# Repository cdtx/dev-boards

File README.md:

Some simple home made PCBs

- [ESP-01 prototyping board](./esp01-1/README.md)

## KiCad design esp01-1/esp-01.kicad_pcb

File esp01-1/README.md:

ESP-01 prototyping board
========================

This board allows to discuss an ESP-01 and program it from a USB connected PC.
So it basically embeds a voltage regulator, and a USB/Serial transceiver.
Push buttons allows to switch to bootloader mode.

ESP-01 is the cheapest ESP8266 based iot component, less than 5$
It's only a wifi modem that's driven by [AT commands](https://room-15.github.io/blog/2015/03/26/esp8266-at-command-reference/#AT), no GPIO, no available peripherals.

Typical case is to connect it with an arduino or equivalent discussing AT commands over tx/rx pins.
Flashing a new firmware can be done over tx/rx as well, after a special boot procedure.

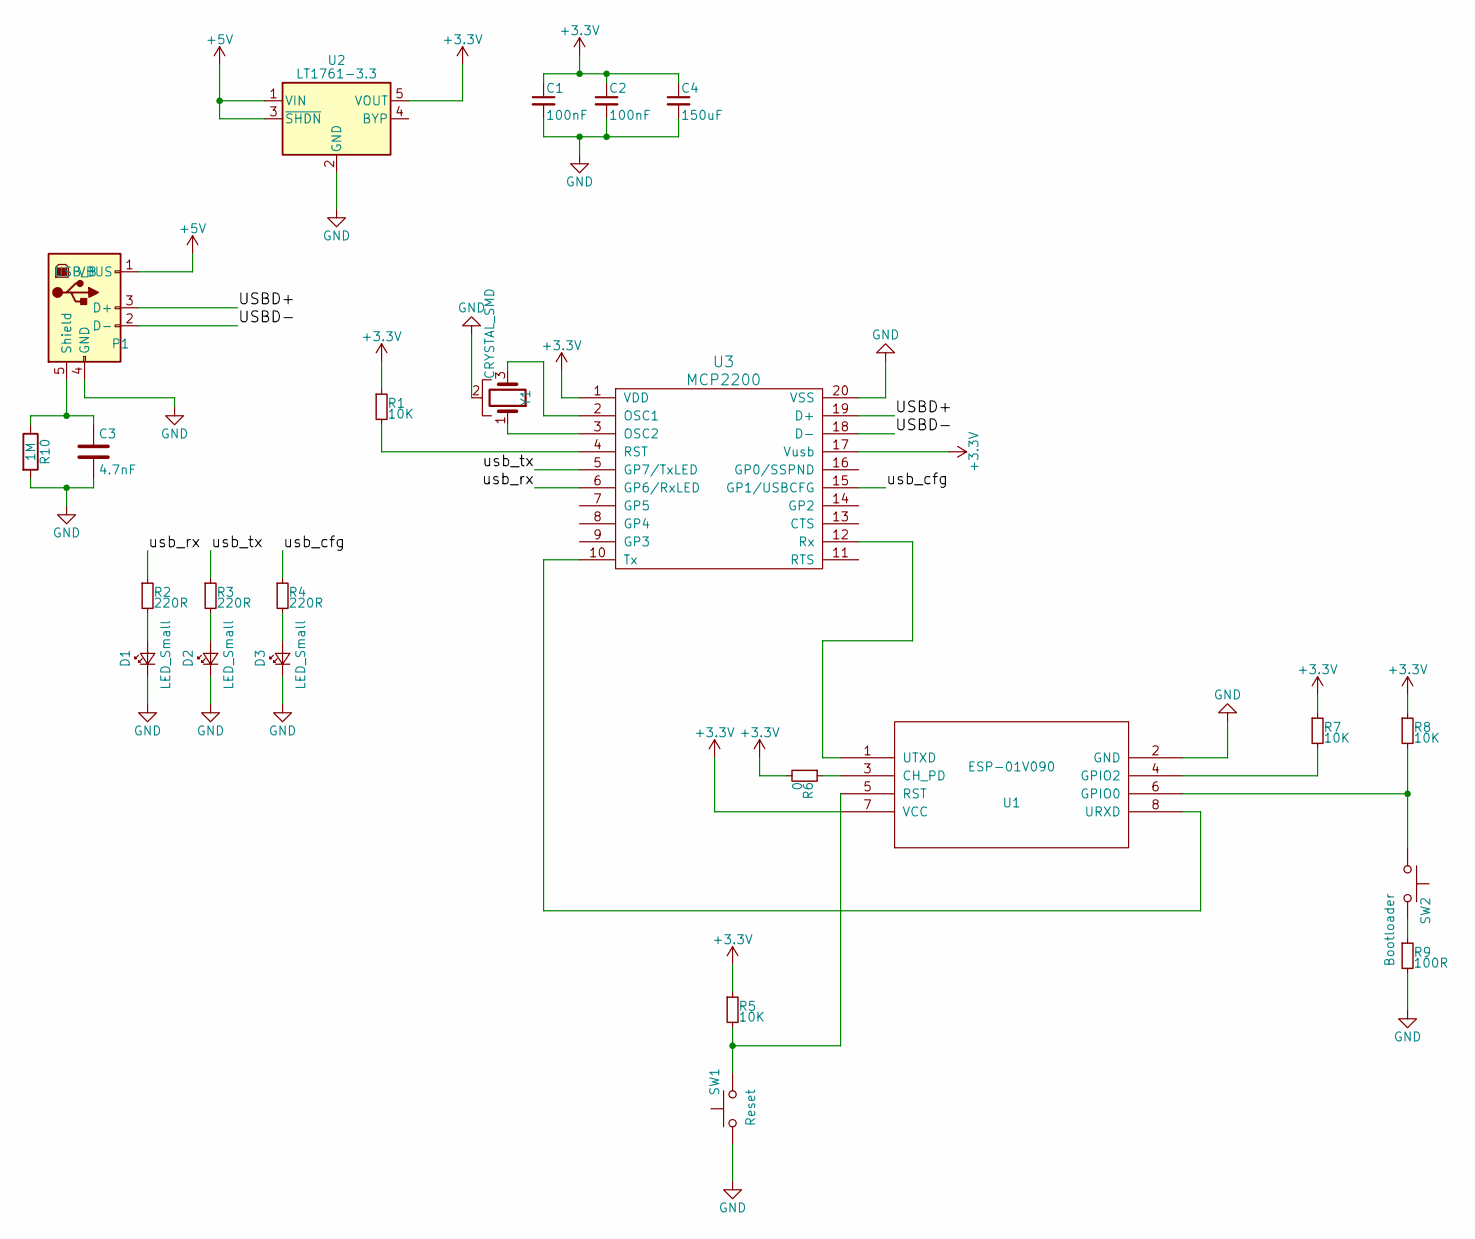
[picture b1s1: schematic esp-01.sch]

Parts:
C1, C2: 100nF; C_0805
C3: 4.7nF; C_Disc_D6_P5
C4: 150uF; C_1210_HandSoldering
D1, D2, D3: LED_Small; LED_1206
P1: USB_B
R1, R7, R8: 10K; Resistor_Horizontal_RM10mm
R2, R3, R4: 220R; Resistor_Horizontal_RM10mm
R5: 10K; R_0603
R6: 0; R_0603
R9: 100R; R_0603
R10: 1M; Resistor_Horizontal_RM10mm
SW1: Reset; SW_PUSH_SMALL
SW2: Bootloader; SW_PUSH_SMALL
U1: ESP-01V090; ESP-01
U2: LT1761-3.3; SOT-23-5
U3: MCP2200; SOIC-20W_7.5x12.8mm_Pitch1.27mm
Y1: CRYSTAL_SMD; Resonator_3.2x1.3mm

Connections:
+3V3: C1.1, C2.1, C4.1, R1.1, R5.1, R6.2, R7.1, R8.1, U1.7 (VCC), U2.5 (VOUT), U3.1 (VDD), U3.17 (Vusb)
+5V: P1.1 (VBUS), U2.1 (VIN), U2.3 (~SHDN)
/USBD+: P1.3 (D+), U3.19 (D+)
/USBD-: P1.2 (D-), U3.18 (D-)
/usb_cfg: R4.1, U3.15 (GP1/USBCFG)
/usb_rx: R2.1, U3.6 (GP6/RxLED)
/usb_tx: R3.1, U3.5 (GP7/TxLED)
GND: C1.2, C2.2, C3.2, C4.2, D1.1 (K), D2.1 (K), D3.1 (K), P1.4 (GND), R9.2, R10.2, SW1.1, U1.2 (GND), U2.2 (GND), U3.20 (VSS), Y1.2
unnamed: C3.1, P1.5 (Shield), R10.1
unnamed: D1.2 (A), R2.2
unnamed: D2.2 (A), R3.2
unnamed: D3.2 (A), R4.2
unnamed: R1.2, U3.4 (RST)
unnamed: R5.2, SW1.2, U1.5 (RST)
unnamed: R6.1, U1.3 (CH_PD)
unnamed: R7.2, U1.4 (GPIO2)
unnamed: R8.2, SW2.1, U1.6 (GPIO0)
unnamed: R9.1, SW2.2
unnamed: U1.1 (UTXD), U3.12 (Rx)
unnamed: U1.8 (URXD), U3.10 (Tx)
unnamed: U3.2 (OSC1), Y1.3
unnamed: U3.3 (OSC2), Y1.1

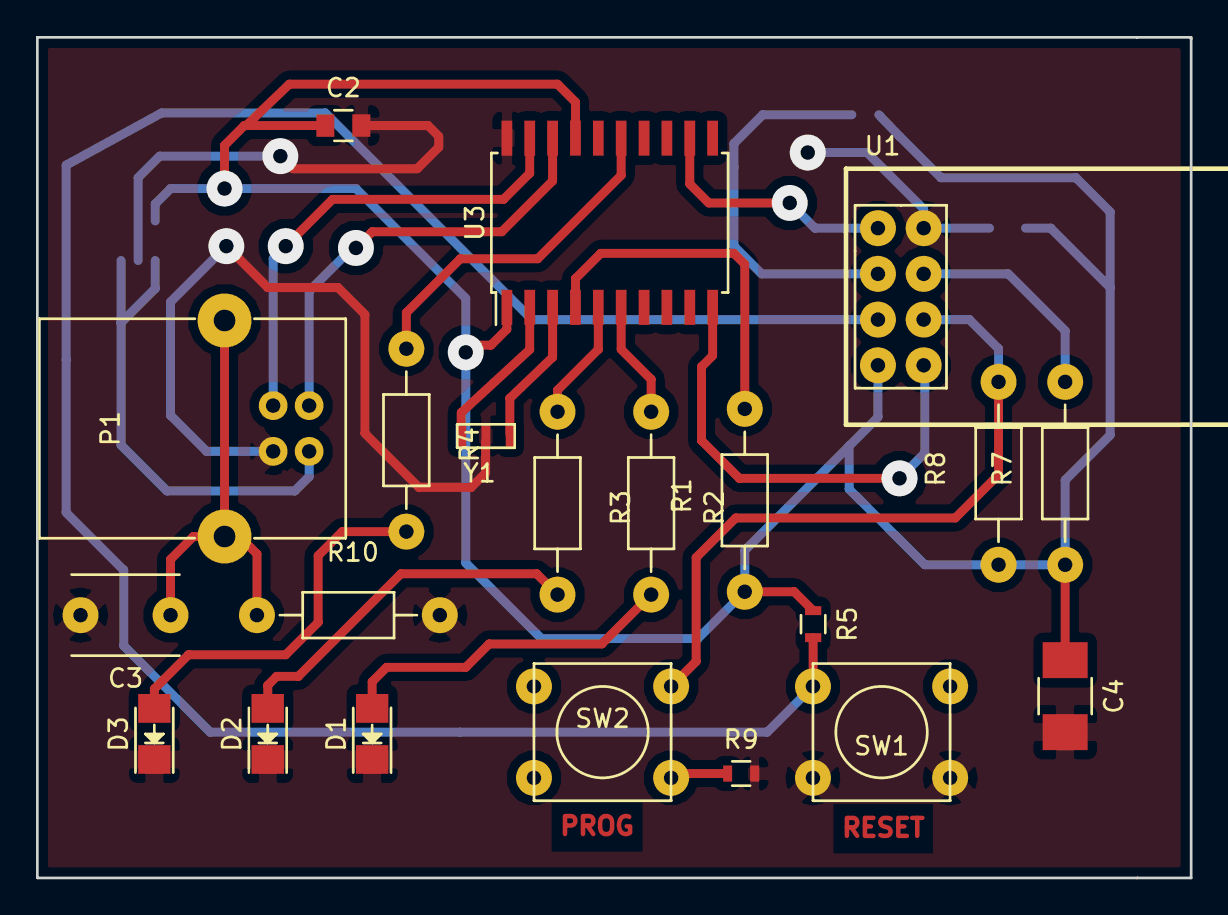
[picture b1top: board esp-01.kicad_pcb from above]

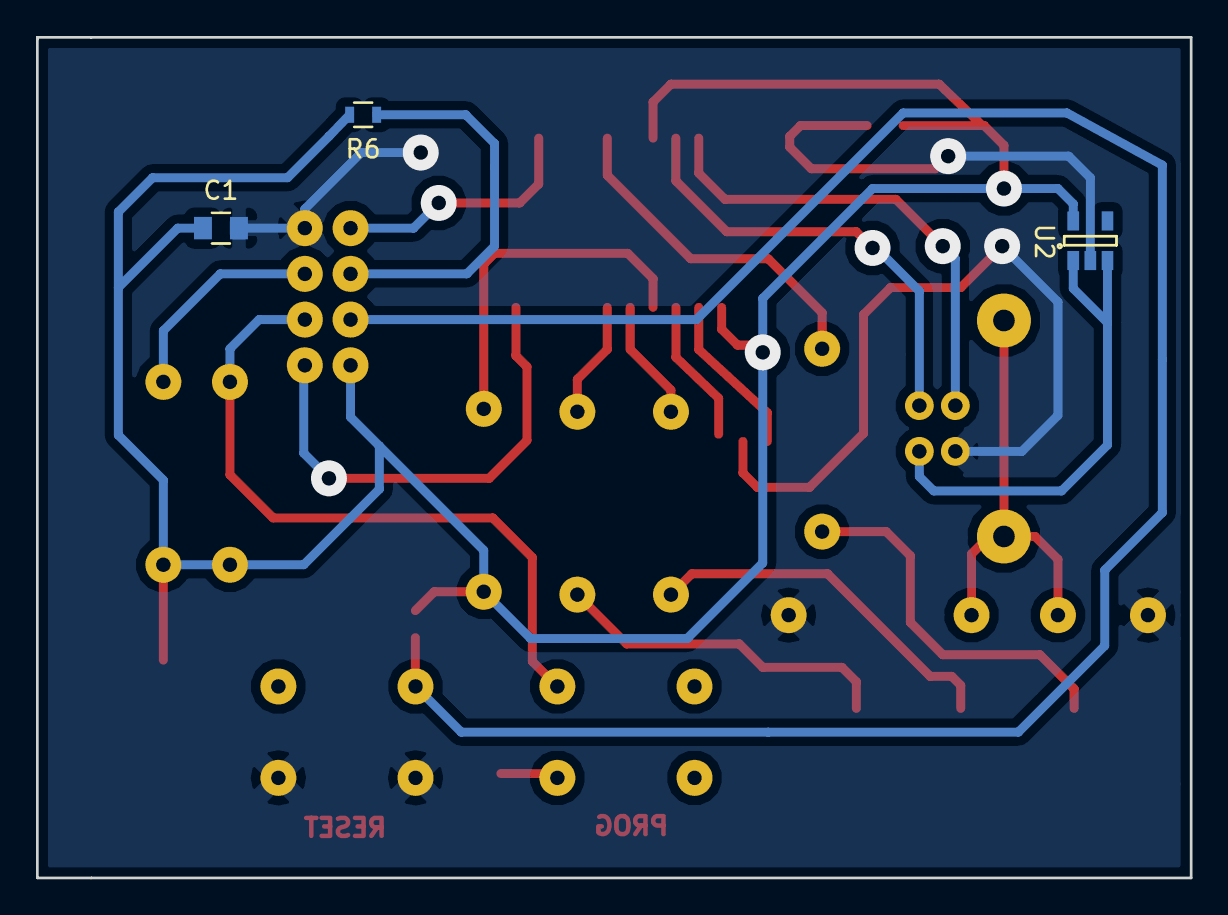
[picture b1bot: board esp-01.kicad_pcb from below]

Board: 2 copper layers, 64.1 x 46.7 mm, 24 parts (3 on the bottom side), 22 nets.

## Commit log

2016-10-04 README
2016-10-14 First scheme and routing
2016-10-17 Reworked the esp-01 board routing
2016-10-17 Added .gitignore and README
2016-10-18 Removed unwanted footprint
2016-10-18 Added layer alignment target
2016-10-20 Fixed design error. The USB ocnnector can only be soldered the background
2016-10-25 Added a big decoupling capacitor because of the ESP current glutony
2016-10-25 Added minimal doc
2016-10-25 Fixed typo
2016-10-25 oopsoops
2017-06-20 Updated project to follow the kicad official libraries evolutions
